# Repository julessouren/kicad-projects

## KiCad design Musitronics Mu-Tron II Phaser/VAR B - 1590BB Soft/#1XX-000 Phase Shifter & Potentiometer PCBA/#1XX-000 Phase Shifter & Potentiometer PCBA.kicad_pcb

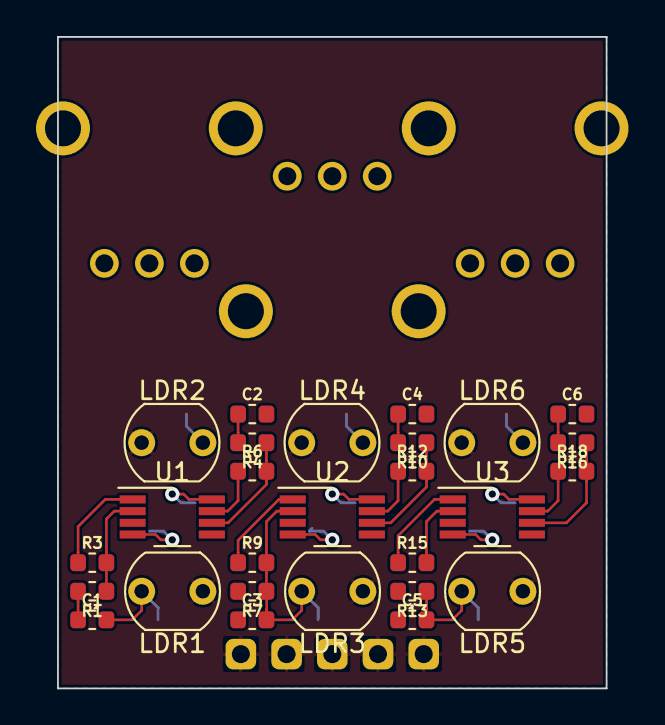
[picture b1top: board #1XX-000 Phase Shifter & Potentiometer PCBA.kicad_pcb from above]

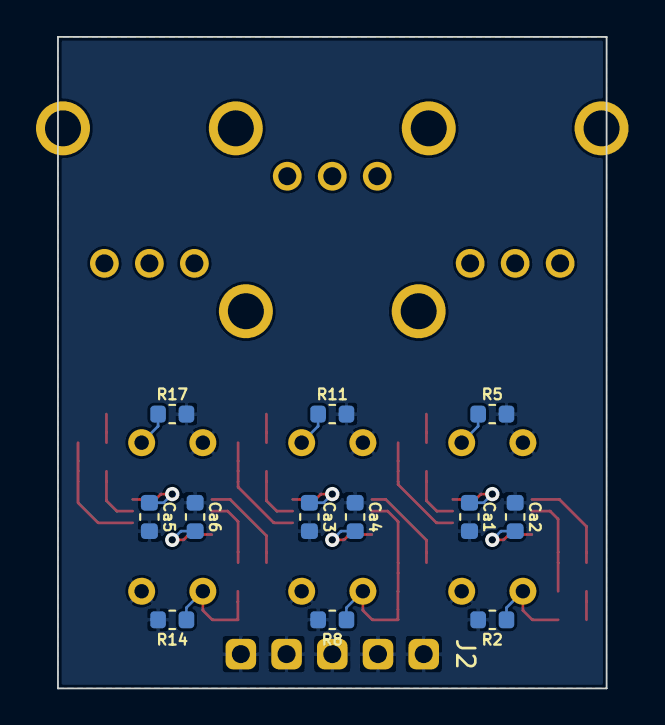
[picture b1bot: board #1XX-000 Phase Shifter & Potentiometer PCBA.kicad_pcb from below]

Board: 2 copper layers, 30.5 x 36.2 mm, 43 parts (16 on the bottom side), 22 nets.

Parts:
C1, C2, C3, C4, C5, C6: 6n8; C_0603_1608M_h0.85
Ca1, Ca2, Ca3, Ca4, Ca5, Ca6: 100n; C_0603_1608M_h0.85
J2: PinHeader_Straight_01x05_P2.54mm; PinHeader_1x05_P2.54mm_Vertical
LDR1, LDR2, LDR3, LDR4, LDR5, LDR6: KE-10720; Waitrony_KE-10720
R1, R3, R4, R6, R7, R9, R10, R12, R13, R15, R16, R18: 4k7; R_0603_1608M
R2, R5, R8, R11, R14, R17: 220k; R_0603_1608M
RV53, RV54: B10k; Alpha_Taiwan_RD901F-40
RV55: A25k; Alpha_Taiwan_RD901F-40
U1, U2, U3: 4558; Texas_Instruments_RC4558IDGKR

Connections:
GND: Ca1.2, Ca2.1, Ca3.2, Ca4.1, Ca5.2, Ca6.1, J2.1, J2.2, J2.3, J2.4, J2.5, LDR1.1, LDR2.1, LDR3.1, LDR4.1, LDR5.1, LDR6.1, R2.2, R5.2, R8.2, R11.2, R14.2, R17.2
unnamed: C1.2, LDR1.2, R2.1, U1.3
unnamed: C2.1, R3.1, R4.2, U1.1
unnamed: C2.2, LDR2.2, R5.1, U1.5
unnamed: C3.1, R6.1, R7.2, U1.7
unnamed: C3.2, LDR3.2, R8.1, U2.3
unnamed: C4.1, R9.1, R10.2, U2.1
unnamed: C4.2, LDR4.2, R11.1, U2.5
unnamed: C5.1, R12.1, R13.2, U2.7
unnamed: C5.2, LDR5.2, R14.1, U3.3
unnamed: C6.1, R15.1, R16.2, U3.1
unnamed: C6.2, LDR6.2, R17.1, U3.5
unnamed: R1.1, R3.2, U1.2
unnamed: R4.1, R6.2, U1.6
unnamed: R7.1, R9.2, U2.2
unnamed: R10.1, R12.2, U2.6
unnamed: R13.1, R15.2, U3.2
unnamed: R16.1, R18.2, U3.6
PHASER_IN: C1.1, R1.2
PHASER_OUT: R18.1, U3.7
VCC: Ca1.1, Ca3.1, Ca5.1, U1.8, U2.8, U3.8
VSS: Ca2.2, Ca4.2, Ca6.2, U1.4, U2.4, U3.4

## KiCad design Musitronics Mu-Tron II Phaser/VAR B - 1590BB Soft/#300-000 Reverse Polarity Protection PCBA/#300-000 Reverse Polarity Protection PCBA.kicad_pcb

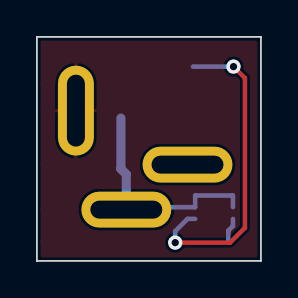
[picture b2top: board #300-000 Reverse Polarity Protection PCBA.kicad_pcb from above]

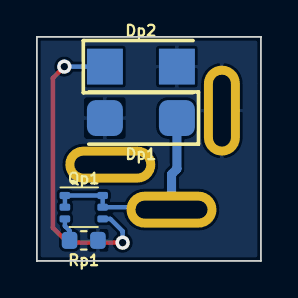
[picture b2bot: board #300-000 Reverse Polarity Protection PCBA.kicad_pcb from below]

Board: 2 copper layers, 12.4 x 12.4 mm, 5 parts (4 on the bottom side), 4 nets.

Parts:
Dp1, Dp2: 1SMA5924BT3G; ON_Semi_1SMA5924BT3G
Ja3: NEB_J_21_C; Lumberg_NEB_J_21_C
Qp1: MCH6341-TL-W; ON_Semi_MCH6341-TL-W
Rp1: 0R; R_0603_1608M

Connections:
GND: Dp1.1, Dp2.1, Ja3.1, Rp1.1
unnamed: Dp1.2, Ja3.2, Qp1.1, Qp1.2, Qp1.5, Qp1.6
unnamed: Qp1.3, Rp1.2
VCC: Dp2.2, Qp1.4

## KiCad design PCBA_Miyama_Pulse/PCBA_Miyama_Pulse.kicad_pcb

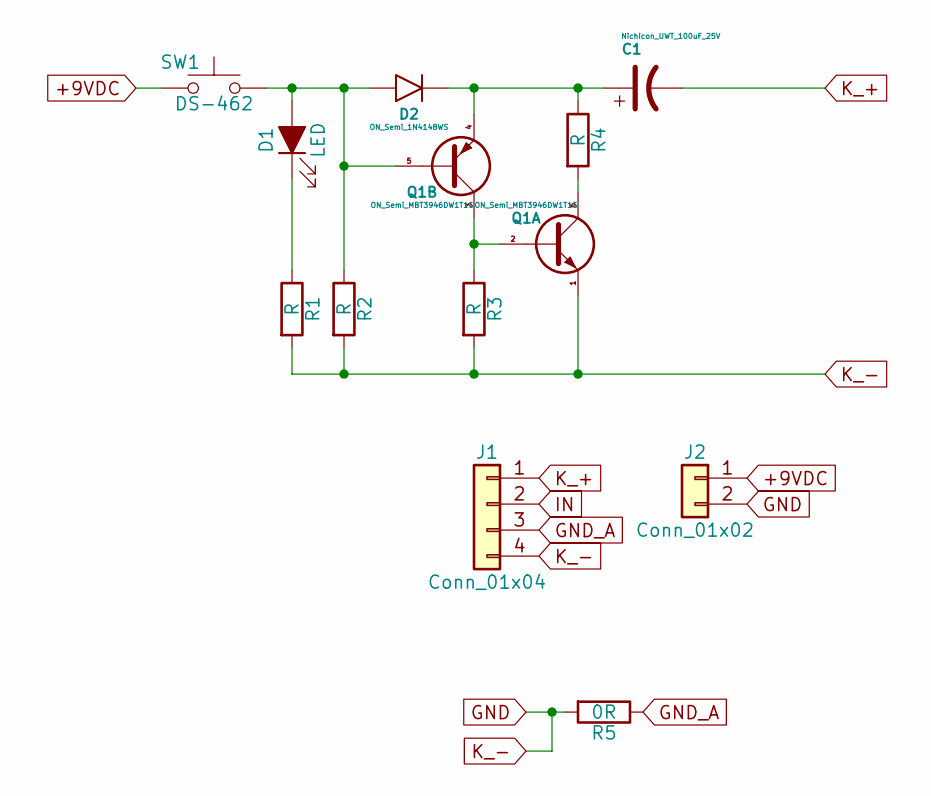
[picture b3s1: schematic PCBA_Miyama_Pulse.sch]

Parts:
C1: Nichicon_UWT_100uF_25V; Nichicon_UWT1E101MCL1GS_100uF_25V_6.3x7.7mm
D1: LED; Wire_Pad_2x_1.0mm_Hole_1.5_Annular_2.54mm_Pitch
D2: ON_Semi_1N4148WS; ON_Semi_1N4148WS_SOD-323F-2
J1: Conn_01x04; PinHeader_1x04_P2.54mm_Vertical
J2: Conn_01x02; PinHeader_1x02_P2.54mm_Vertical
Q1: ON_Semi_MBT3946DW1T1G; ON_Semi_MBT3946DW1T1G_SOT-363_SC-70-6_SC-80
R1, R2, R3, R4: R; R_0603_1608M
R5: 0R; R_0603_1608M
SW1: DS-462; Miyama_DS-462

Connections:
+9VDC: J2.1, SW1.2
GND: J1.4, J2.2, Q1.1 (E1), R1.2, R2.2, R3.2, R5.2
GND_A: J1.3, R5.1
IN: J1.2
K_+: C1.2, J1.1
unnamed: C1.1, D2.1 (K), Q1.4 (E2), R4.1
unnamed: D1.1 (K), R1.1
unnamed: D1.2 (A), D2.2 (A), Q1.5 (B2), R2.1, SW1.1
unnamed: Q1.2 (B1), Q1.3 (C2), R3.1
unnamed: Q1.6 (C1), R4.2

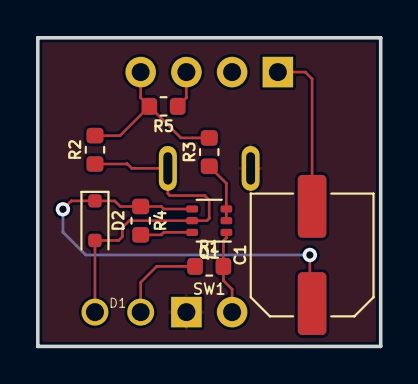
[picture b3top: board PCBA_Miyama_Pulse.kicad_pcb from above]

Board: 2 copper layers, 19.0 x 17.1 mm, 12 parts (0 on the bottom side), 9 nets.

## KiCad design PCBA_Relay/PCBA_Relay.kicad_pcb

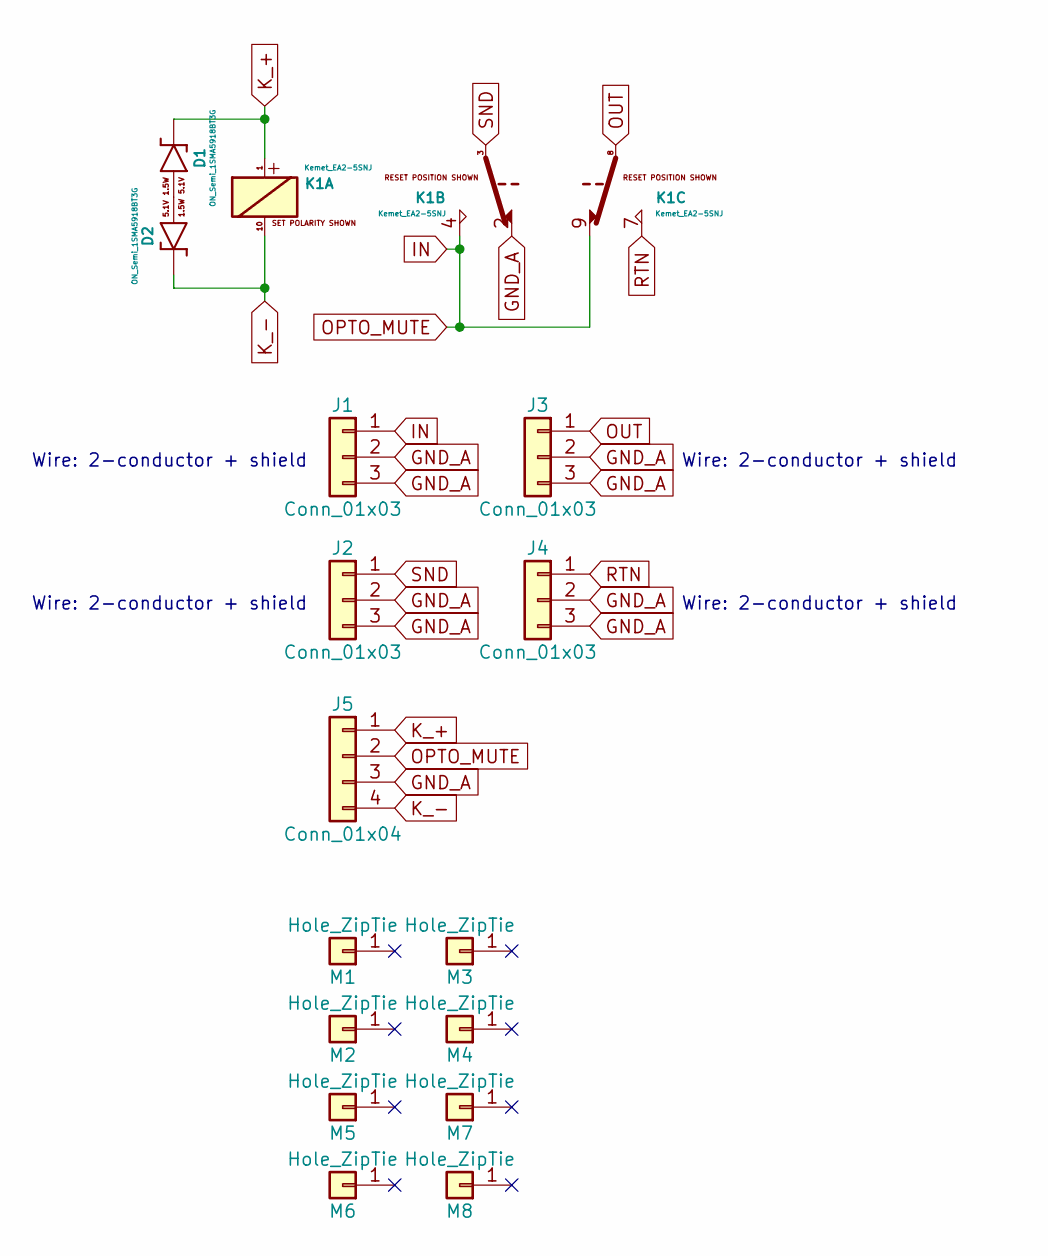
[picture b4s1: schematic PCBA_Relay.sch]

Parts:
D1, D2: ON_Semi_1SMA5918BT3G; ON_Semi_1SMA5918BT3G_SMA_DO-214AC
J1, J2, J3, J4: Conn_01x03; Wire_Pad_3x_1.2mm_Hole_2.0_Annular_2.54mm_Pitch
J5: Conn_01x04; PinHeader_1x04_P2.54mm_Vertical
K1: Kemet_EA2-5SNJ
M1, M2, M3, M4, M5, M6, M7, M8: Hole_ZipTie; ZipTie_Hole_1.8x0.8_PTH_0.2_mm_Annular

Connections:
GND_A: J1.2, J1.3, J2.2, J2.3, J3.2, J3.3, J4.2, J4.3, J5.3, K1.2
IN: J1.1, J5.2, K1.4, K1.9
K_+: D1.1 (K), J5.1, K1.1
K_-: D2.1 (K), J5.4, K1.10
unnamed: D1.2 (A), D2.2 (A)
OUT: J3.1, K1.8
RTN: J4.1, K1.7
SND: J2.1, K1.3

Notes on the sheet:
Wire: 2-conductor + shield

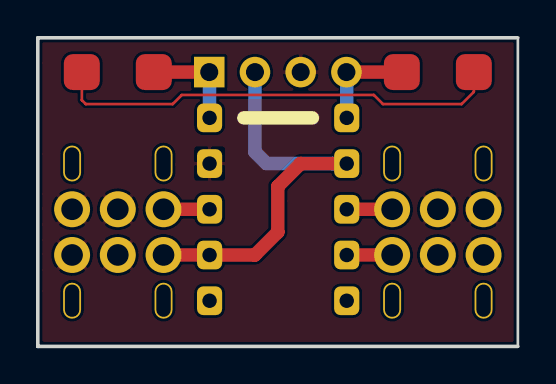
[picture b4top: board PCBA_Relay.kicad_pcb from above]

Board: 2 copper layers, 26.7 x 17.1 mm, 16 parts (0 on the bottom side), 8 nets.

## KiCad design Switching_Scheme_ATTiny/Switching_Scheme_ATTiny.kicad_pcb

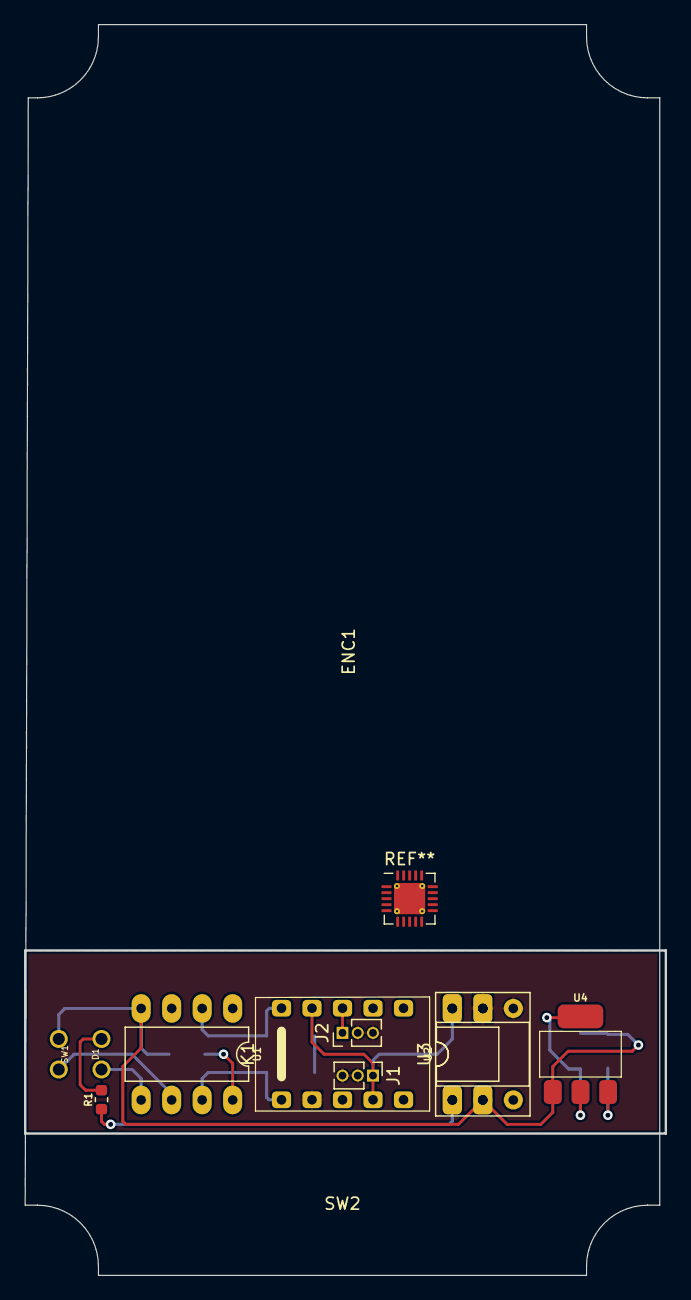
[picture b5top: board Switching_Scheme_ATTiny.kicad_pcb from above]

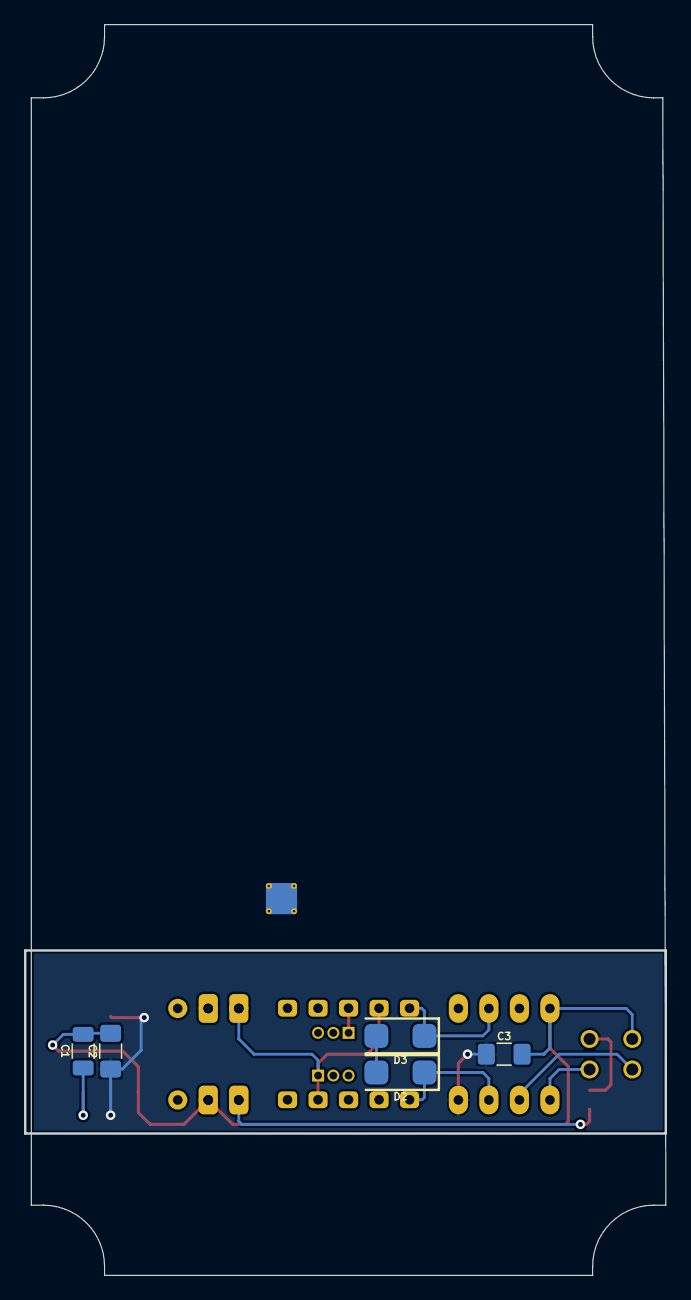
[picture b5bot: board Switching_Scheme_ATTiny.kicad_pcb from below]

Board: 2 copper layers, 53.3 x 104.1 mm, 17 parts (5 on the bottom side), 13 nets.

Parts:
C1: 10uF/cer; C_1206_3216M
C2: 4.7uF/cer/lowESR; C_1206_3216M_HandSolder
C3: 100n/decoupling; C_1206_3216M_HandSolder
D1: LED_ALT; Wire_Pad_2x_1.0mm_Hole_1.5_Annular_2.54mm_Pitch
D2, D3: ON_Semi_1SMA5918BT3G; ON_Semi_1SMA5918BT3G_SMA_DO-214AC
ENC1: 1590B; Hammond_1590B
J1, J2: Conn_01x03; PinHeader_1x03_P1.27mm_Vertical
K1: Kemet_EA2-5SNJ
R1: R; R_0603_1608M
SW1: SW_Push; Wire_Pad_2x_1.0mm_Hole_1.5_Annular_2.54mm_Pitch
SW2: NO_MOM; Switch_NO_MOM
U1: Atmel_ATtiny85-20PU; Atmel_ATtiny85-20PU_DIP-8_Socketed
U2: Toshiba_TLP222A(F); Toshiba_TLP222A(F)_DIP-4_Socketed
U3: Fairchild_H11F1M; DIP-6_W7.62mm_Socket
U4: NCP1117LPST50T3G; ON_Semi_NCP1117LPST50T3G_SOT-223-3

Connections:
+5.0VDC: C2.1, C3.1, U1.8, U4.2
+9.0VDC: C1.1, U4.3
/OPTO_A: R1.1, U2.1, U3.1
GND_A: J1.2, J1.3, J2.2, J2.3, K1.2, U2.3, U3.4, U3.5
GND_D: C1.2, C2.2, C3.2, SW1.2, U1.4, U2.2, U3.2, U4.1
IN: J1.1, K1.4, K1.9, U2.4, U3.6
unnamed: D1.1, R1.2
unnamed: D2.2, D3.2
OUT: J2.1, K1.8
UC_MUTE: D1.2, U1.5
UC_REL_RST: D3.1, K1.10, U1.2
UC_REL_SET: D2.1, K1.1, U1.7
UC_SWITCH: SW1.1, U1.6

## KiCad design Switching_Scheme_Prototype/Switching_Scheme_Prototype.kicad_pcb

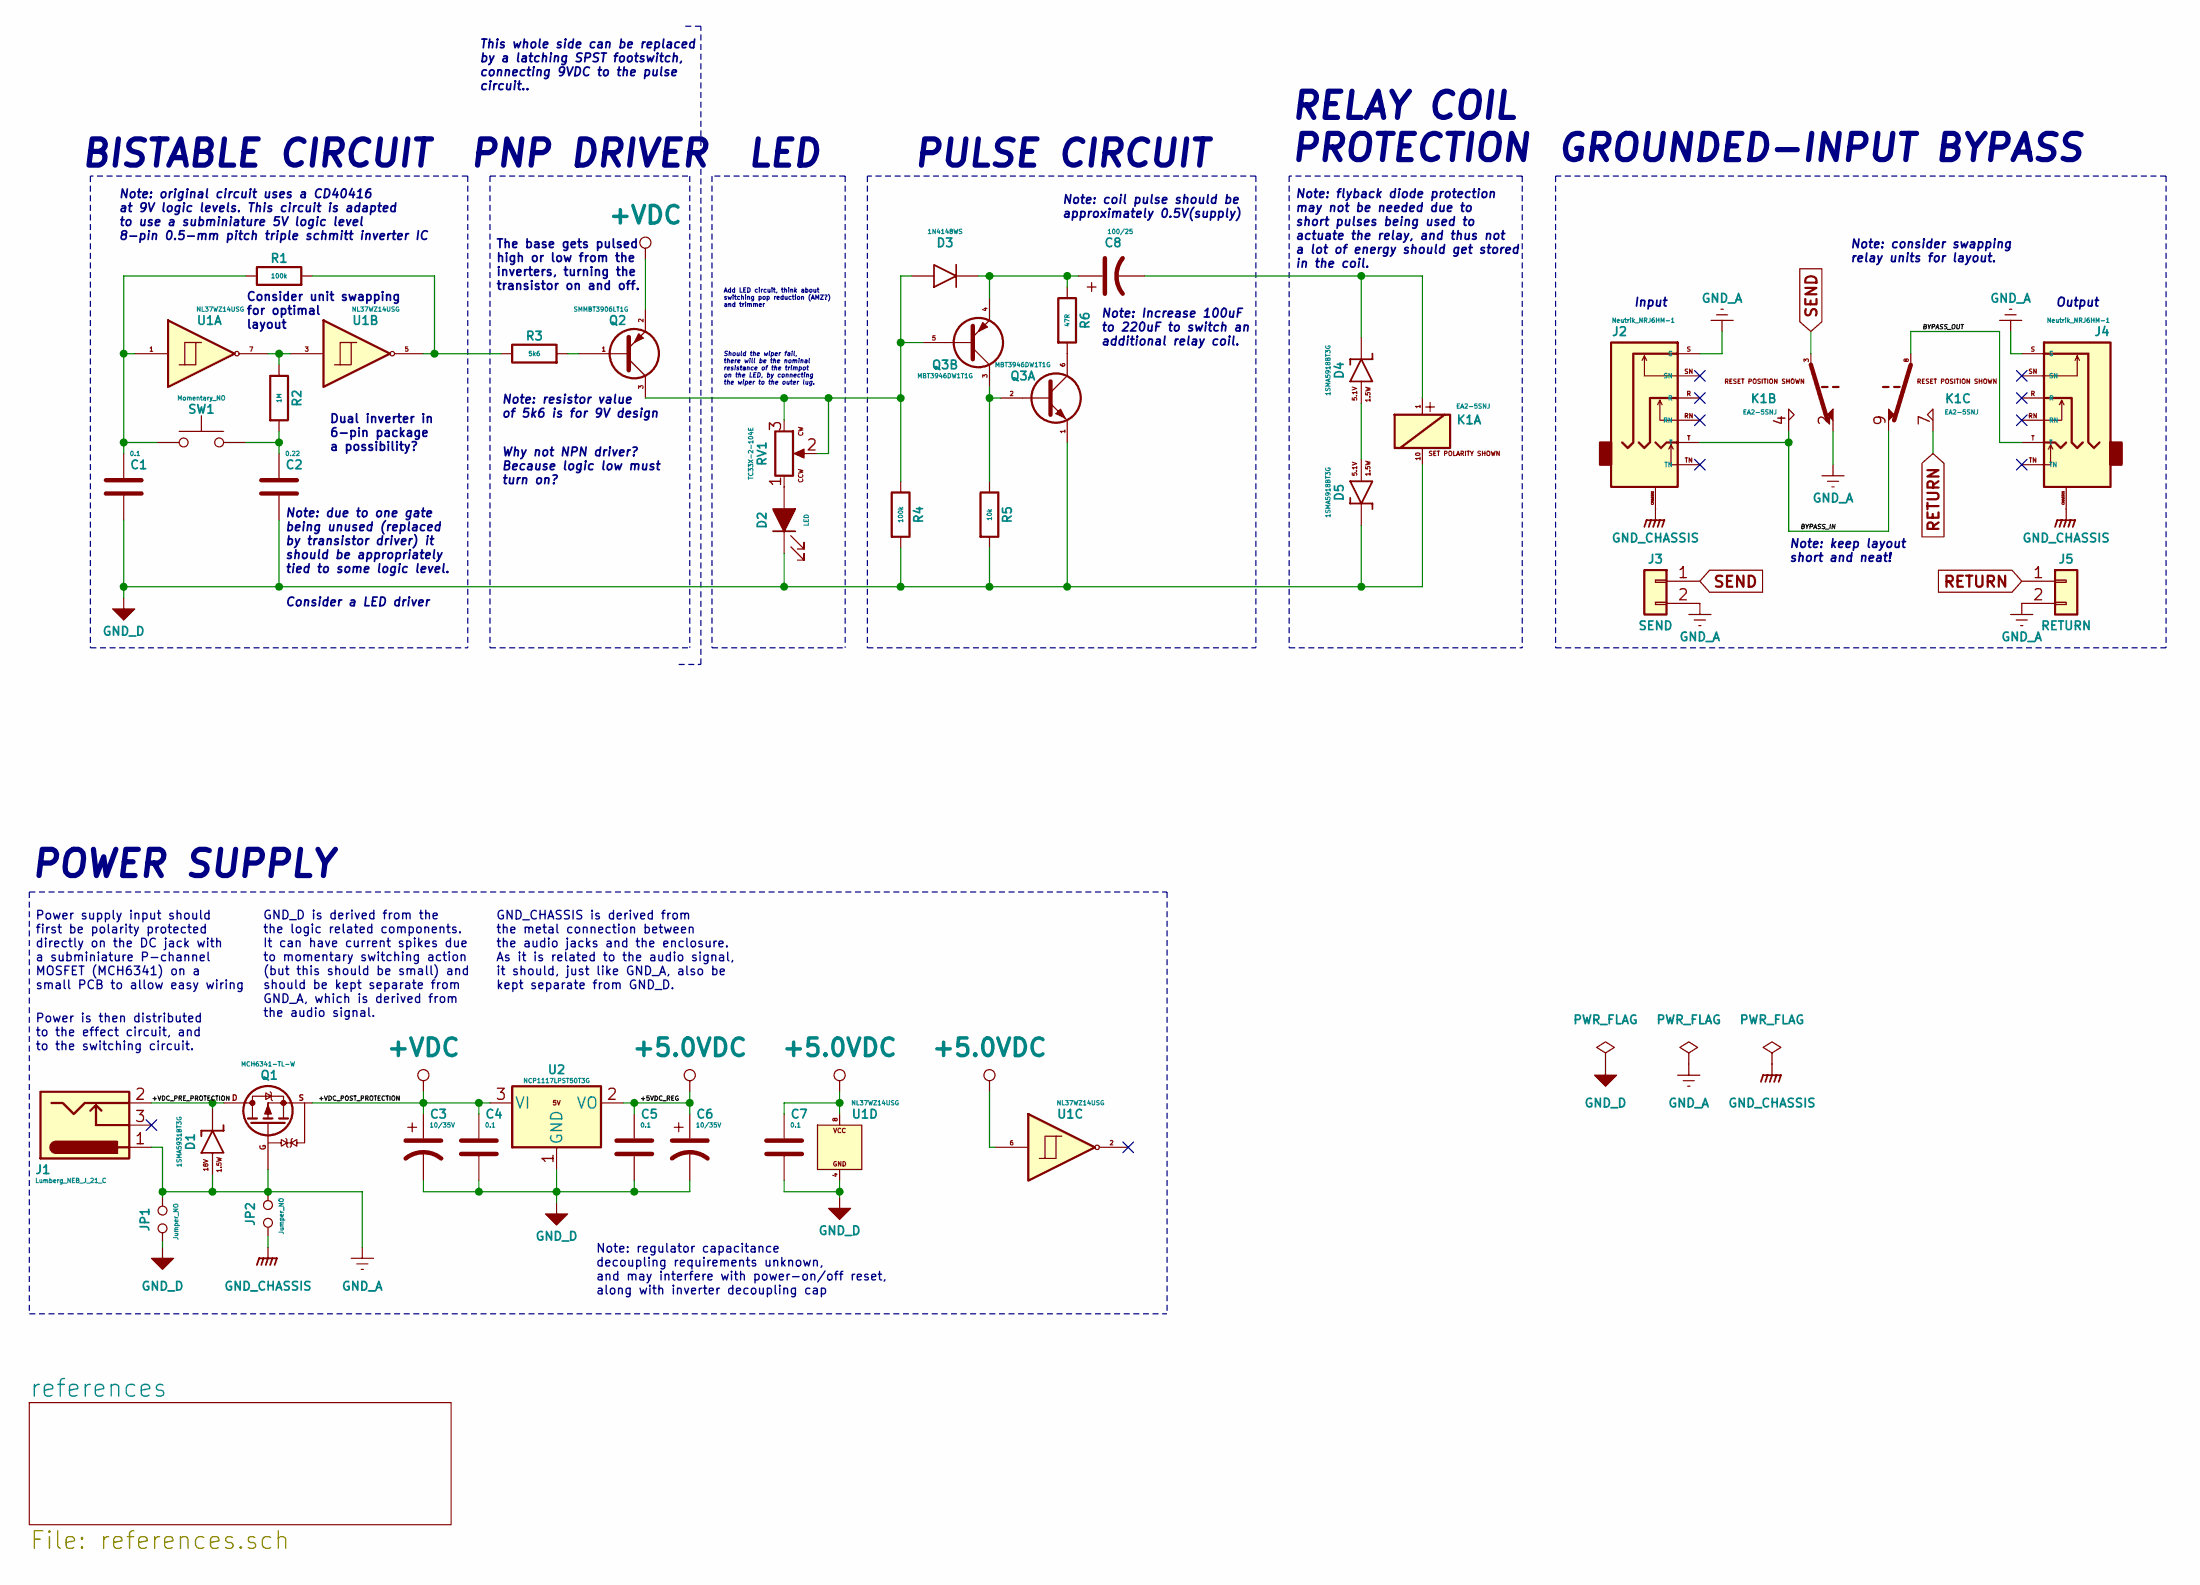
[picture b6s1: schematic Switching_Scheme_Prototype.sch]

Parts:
C1, C4, C5, C7: 0.1; C_1206_3216M
C2: 0.22; C_1206_3216M
C3, C6: 10/35V; Nichicon_UWT1V100MCL1GB_10uF_35V_5.0x5.4mm
C8: 100/25; Nichicon_UWT1E101MCL1GS_100uF_25V_6.3x7.7mm
D1: 1SMA5931BT3G; ON_Semi_1SMA5931BT3G_SMA_DO-214AC
D2: LED; PinHeader_1x02_P2.54mm_Vertical_Top
D3: 1N4148WS; ON_Semi_1N4148WS_SOD-323F-2
D4, D5: 1SMA5918BT3G; ON_Semi_1SMA5918BT3G_SMA_DO-214AC
J1: Lumberg_NEB_J_21_C; Lumberg_NEB_J_21_C_FitsModel_Top
J2, J4: Neutrik_NRJ6HM-1
J3: SEND; PinHeader_1x02_P2.54mm_Vertical_Top
J5: RETURN; PinHeader_1x02_P2.54mm_Vertical_Top
JP1, JP2: Jumper_NO; PinHeader_1x02_P2.54mm_Vertical_Top
K1: EA2-5SNJ; Kemet_EA2-5SNJ
Q1: MCH6341-TL-W; ON_Semi_MCH6341-TL-W_SOT-363_SC-70-6_SC-88
Q2: SMMBT3906LT1G; ON_Semi_SMMBT3906LT1G_SOT-23-3
Q3: MBT3946DW1T1G; ON_Semi_MBT3946DW1T1G_SOT-363_SC-70-6_SC-80
R1, R4: 100k; R_1206_3216M
R2: 1M; R_1206_3216M
R3: 5k6; R_1206_3216M
R5: 10k; R_1206_3216M
R6: 47R; R_1206_3216M
RV1: TC33X-2-104E; Bourns_TC33X-2-104E
SW1: Momentary_NO; PinHeader_1x02_P2.54mm_Vertical_Top
U1: NL37WZ14USG; ON_Semi_NL37WZ14USG_US8-8
U2: NCP1117LPST50T3G; ON_Semi_NCP1117LPST50T3G_SOT-223-3

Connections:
+5.0VDC: C5.1, C6.1, C7.1, U1.6, U1.8, U2.2 (VO)
+VDC: C3.1, C4.1, Q1.S, Q2.2 (E), U2.3 (VI)
/+VDC_PRE_PROTECTION: D1.1 (K), J1.2, Q1.D
/BYPASS_IN: J2.T, K1.4, K1.9
/BYPASS_OUT: J4.T, K1.8
GND_A: D1.2 (A), J1.1, J2.S, J3.2, J4.S, J5.2, JP1.1, JP2.1, K1.2, Q1.G
GND_CHASSIS: J2.CHASSIS, J4.CHASSIS, JP2.2
GND_D: C1.2, C2.2, C3.2, C4.2, C5.2, C6.2, C7.2, D2.1 (K), D5.1 (K), JP1.2, K1.10, Q3.1 (E1), R4.2, R5.2, U1.4, U2.1 (GND)
unnamed: C1.1, R1.1, SW1.1, U1.1
unnamed: C2.1, R2.2, SW1.2
unnamed: C8.1, D3.1 (K), Q3.4 (E2), R6.1
unnamed: C8.2, D4.1 (K), K1.1
unnamed: D2.2 (A), RV1.1
unnamed: D3.2 (A), Q2.3 (C), Q3.5 (B2), R4.1, RV1.2, RV1.3
unnamed: D4.2 (A), D5.2 (A)
unnamed: Q2.1 (B), R3.2
unnamed: Q3.2 (B1), Q3.3 (C2), R5.1
unnamed: Q3.6 (C1), R6.2
unnamed: R1.2, R3.1, U1.5
unnamed: R2.1, U1.3, U1.7
RETURN: J5.1, K1.7
SEND: J3.1, K1.3

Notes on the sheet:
POWER SUPPLY
BISTABLE CIRCUIT
Note: regulator capacitance decoupling requirements unknown, and may interfere with power-on/off reset, along with inverter decoupling cap
Note: Increase 100uF to 220uF to switch an additional relay coil.
PNP DRIVER
Note: resistor value of 5k6 is for 9V design
PULSE CIRCUIT
RELAY COIL PROTECTION
GROUNDED-INPUT BYPASS
Input
Output
Power supply input should first be polarity protected directly on the DC jack with a subminiature P-channel MOSFET (MCH6341) on a small PCB to allow easy wiring
Power is then distributed to the effect circuit, and to the switching circuit.
GND_CHASSIS is derived from the metal connection between the audio jacks and the enclosure. As it is related to the audio signal, it should, just like GND_A, also be kept separate from GND_D.
GND_D is derived from the the logic related components. It can have current spikes due to momentary switching action (but this should be small) and should be kept separate from GND_A, which is derived from the audio signal.
Add LED circuit, think about switching pop reduction (AMZ?) and trimmer
Note: coil pulse should be approximately 0.5V(supply)
This whole side can be replaced by a latching SPST footswitch, connecting 9VDC to the pulse circuit..
Why not NPN driver? Because logic low must turn on?
Note: original circuit uses a CD40416 at 9V logic levels. This circuit is adapted to use a subminiature 5V logic level 8-pin 0.5-mm pitch triple schmitt inverter IC
Note: due to one gate being unused (replaced by transistor driver) it should be appropriately tied to some logic level.
Dual inverter in 6-pin package a possibility?
Consider a LED driver
Consider unit swapping for optimal layout
The base gets pulsed high or low from the inverters, turning the transistor on and off.
LED
Should the wiper fail, there will be the nominal resistance of the trimpot on the LED, by connecting the wiper to the outer lug.
Note: flyback diode protection may not be needed due to short pulses being used to actuate the relay, and thus not a lot of energy should get stored in the coil.
Note: keep layout short and neat!
Note: consider swapping relay units for layout.

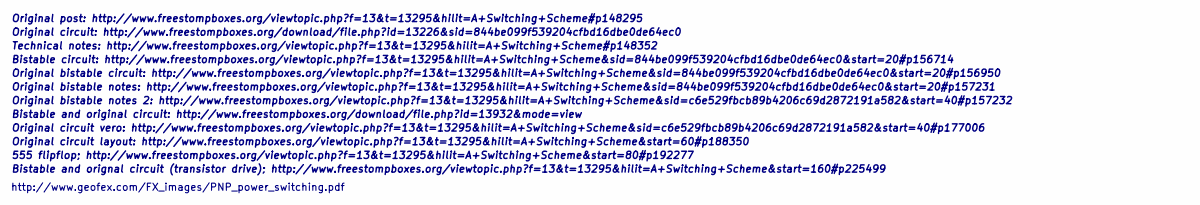
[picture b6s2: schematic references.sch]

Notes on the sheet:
Original post: http://www.freestompboxes.org/viewtopic.php?f=13&t=13295&hilit=A+Switching+Scheme#p148295
Original circuit: http://www.freestompboxes.org/download/file.php?id=13226&sid=844be099f539204cfbd16dbe0de64ec0
Technical notes: http://www.freestompboxes.org/viewtopic.php?f=13&t=13295&hilit=A+Switching+Scheme#p148352
Bistable circuit: http://www.freestompboxes.org/viewtopic.php?f=13&t=13295&hilit=A+Switching+Scheme&sid=844be099f539204cfbd16dbe0de64ec0&start=20#p156714
Original bistable circuit: http://www.freestompboxes.org/viewtopic.php?f=13&t=13295&hilit=A+Switching+Scheme&sid=844be099f539204cfbd16dbe0de64ec0&start=20#p156950
Original bistable notes: http://www.freestompboxes.org/viewtopic.php?f=13&t=13295&hilit=A+Switching+Scheme&sid=844be099f539204cfbd16dbe0de64ec0&start=20#p157231
Original bistable notes 2: http://www.freestompboxes.org/viewtopic.php?f=13&t=13295&hilit=A+Switching+Scheme&sid=c6e529fbcb89b4206c69d2872191a582&start=40#p157232
Bistable and original circuit: http://www.freestompboxes.org/download/file.php?id=13932&mode=view
Original circuit vero: http://www.freestompboxes.org/viewtopic.php?f=13&t=13295&hilit=A+Switching+Scheme&sid=c6e529fbcb89b4206c69d2872191a582&start=40#p177006
Original circuit layout: http://www.freestompboxes.org/viewtopic.php?f=13&t=13295&hilit=A+Switching+Scheme&start=60#p188350
555 flipflop; http://www.freestompboxes.org/viewtopic.php?f=13&t=13295&hilit=A+Switching+Scheme&start=80#p192277
http://www.geofex.com/FX_images/PNP_power_switching.pdf
Bistable and orignal circuit (transistor drive); http://www.freestompboxes.org/viewtopic.php?f=13&t=13295&hilit=A+Switching+Scheme&start=160#p225499

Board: 2 copper layers, 34 parts (0 on the bottom side), 22 nets, no tracks yet.
